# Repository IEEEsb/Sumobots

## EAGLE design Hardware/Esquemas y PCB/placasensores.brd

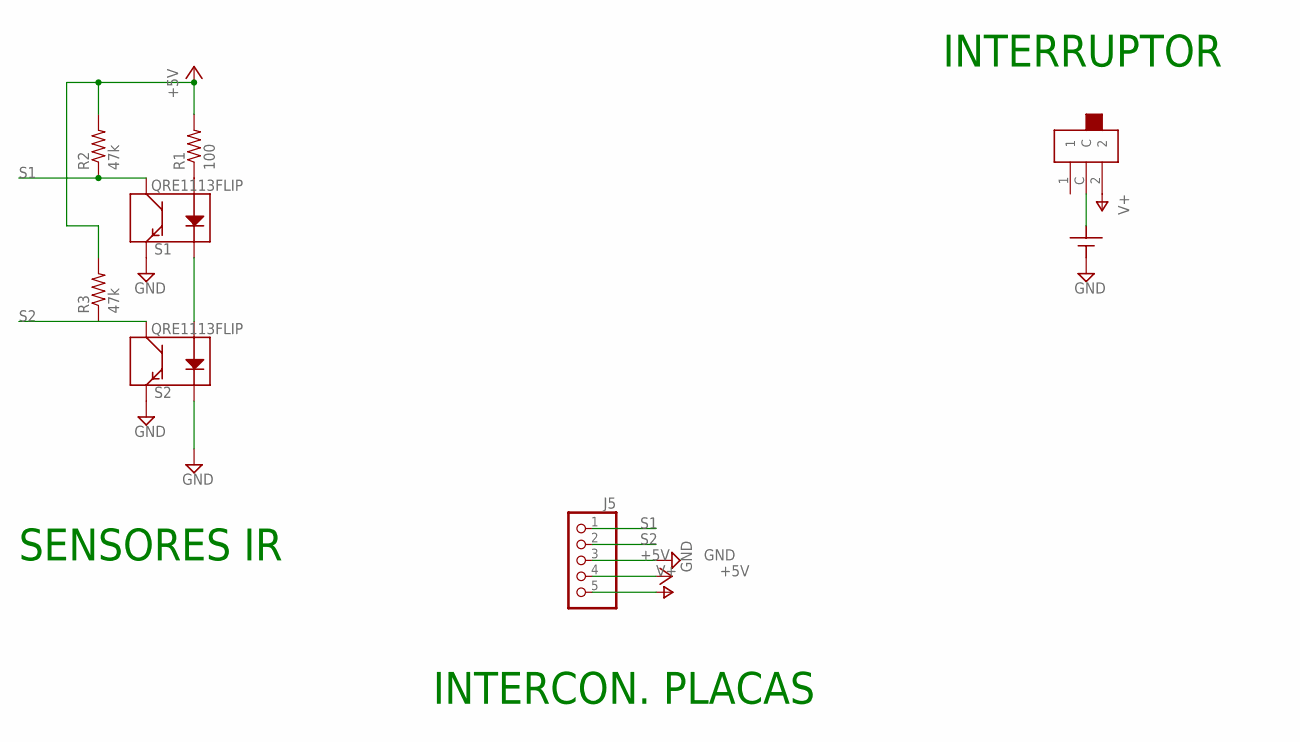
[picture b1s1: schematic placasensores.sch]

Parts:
J5: PINHD-1X5; 1X05
R1: 100; 1206
R2, R3: 47k; 1206
S1, S2: QRE1113FLIP; QRE1113GR_HOLE
SW1: SK-12D07G3
U$3: 5XAA; 5XAAHOLDER

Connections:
+5V: J5.4, R1.2, R2.2, R3.2
GND: J5.3, S1.E, S2.E, S2.K, U$3.P$2
unnamed: S1.K, S2.A
unnamed: R1.1, S1.A
unnamed: SW1.C, U$3.P$1
S1: J5.1, R2.1, S1.C
S2: J5.2, R3.1, S2.C
V+: J5.5, SW1.2

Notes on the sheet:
SENSORES IR
INTERCON. PLACAS
INTERRUPTOR

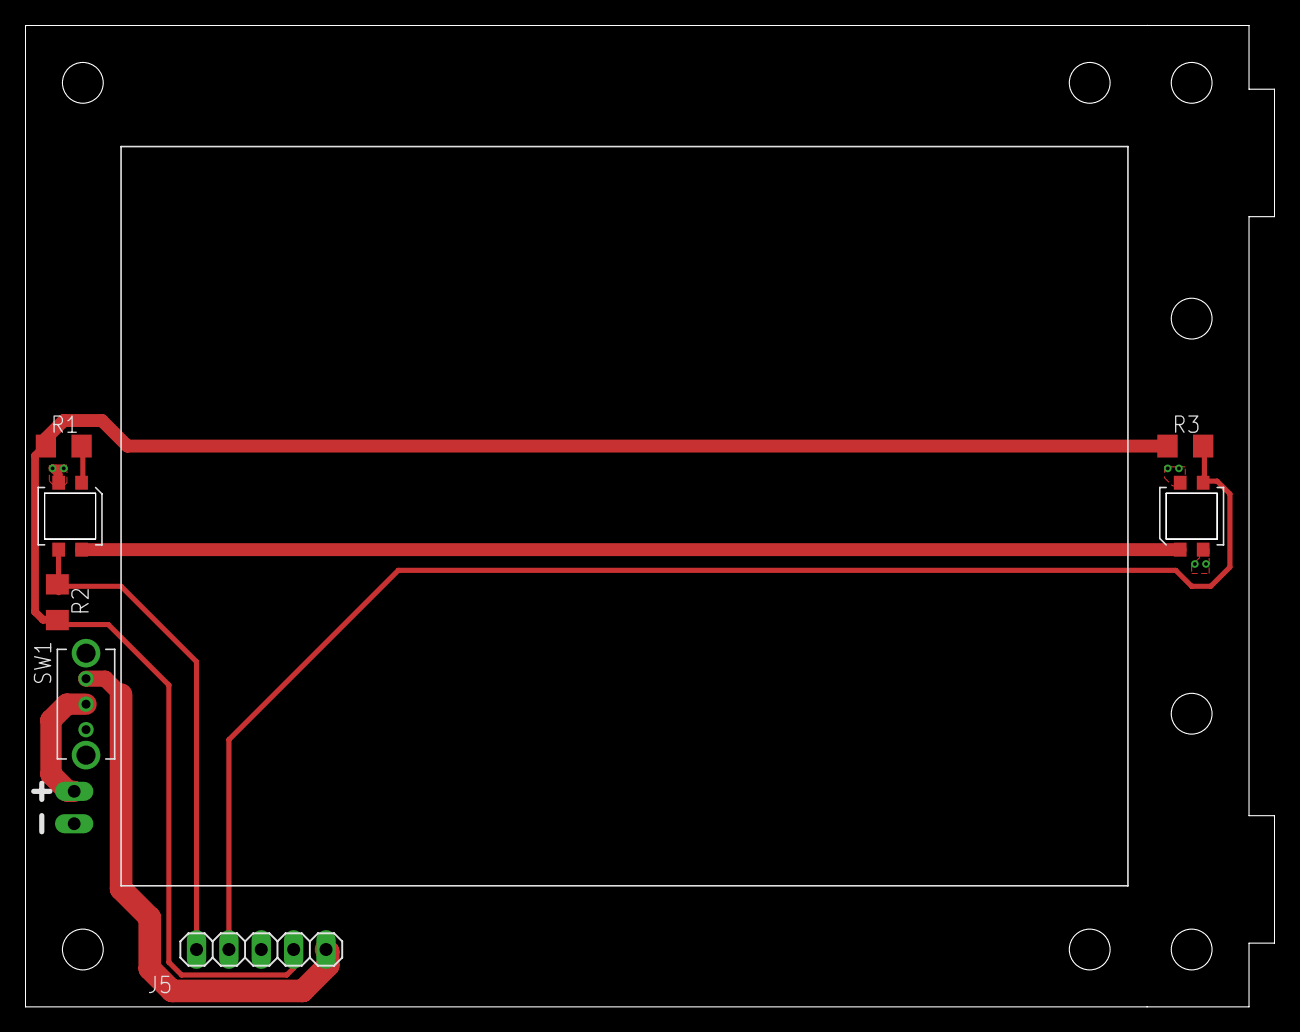
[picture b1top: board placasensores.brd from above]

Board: 2 copper layers, 98.0 x 77.0 mm, 8 parts (0 on the bottom side), 8 nets.

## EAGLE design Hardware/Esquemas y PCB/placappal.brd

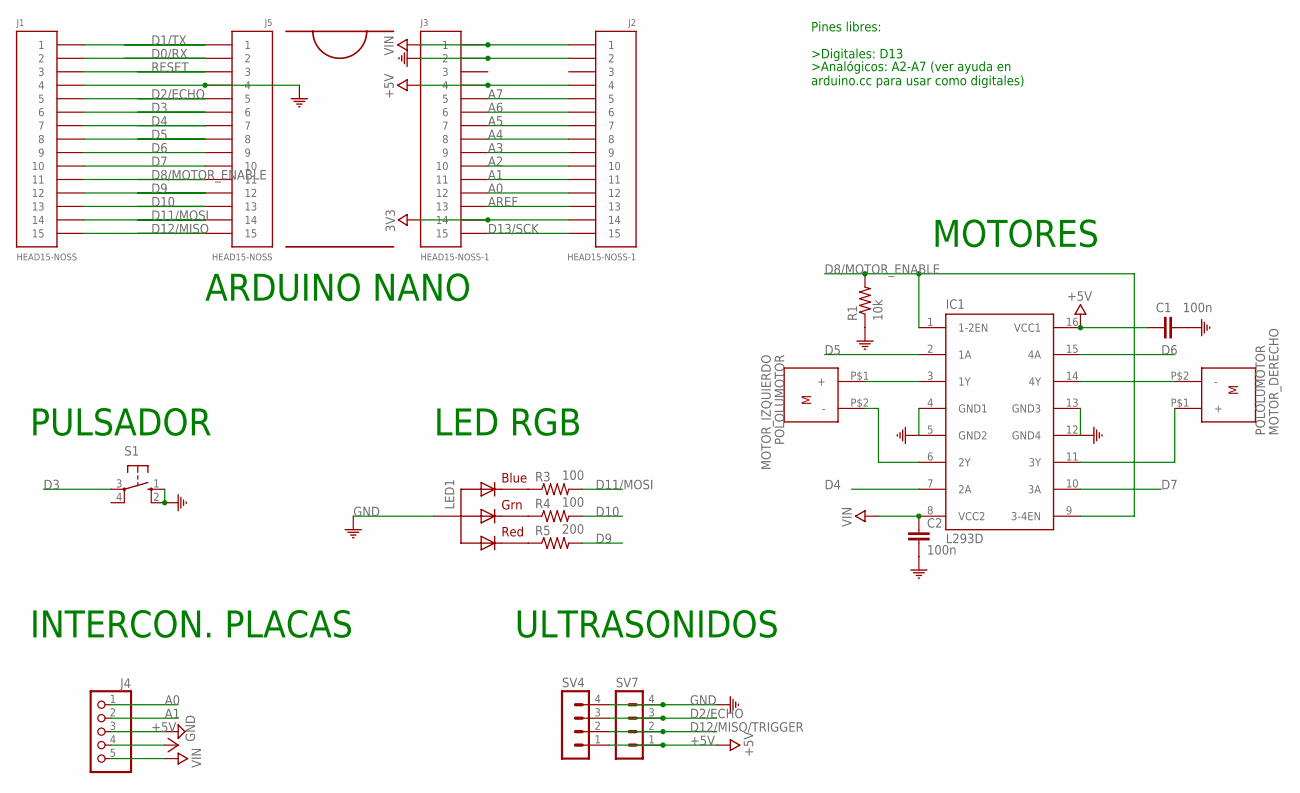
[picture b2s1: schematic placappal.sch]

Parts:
C1, C2: 100n; 1206
IC1: L293D; DIL16
J1, J5: HEAD15-NOSS
J2, J3: HEAD15-NOSS-1
J4: PINHD-1X5; 1X05
LED1: RGBLED_CA-5MM; LED5MMRGB
MOTOR_DERECHO: POLOLUMOTOR; N20MOTOR
MOTOR_IZQUIERDO: POLOLUMOTOR; N20MOTOR
R1: 10k; 1206
R3, R4: 100; 1206
R5: 200; 1206
S1: 10-XX; B3F-10XX
SV4, SV7: MA04-1

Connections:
3V3: J2.14, J3.14
+5V: C1.2, IC1.16 (VCC1), J2.4, J3.4, J4.4, SV4.1, SV7.1
A0: J2.12, J3.12, J4.1
A1: J2.11, J3.11, J4.2
A2: J2.10, J3.10
A3: J2.9, J3.9
A4: J2.8, J3.8
A5: J2.7, J3.7
A6: J2.6, J3.6
A7: J2.5, J3.5
AREF: J2.13, J3.13
D0/RX: J1.2, J5.2
D1/TX: J1.1, J5.1
D2/ECHO: J1.5, J5.5, SV4.3, SV7.3
D3: J1.6, J5.6, S1.3
D4: IC1.7 (2A), J1.7, J5.7
D5: IC1.2 (1A), J1.8, J5.8
D6: IC1.15 (4A), J1.9, J5.9
D7: IC1.10 (3A), J1.10, J5.10
D8/MOTOR_ENABLE: IC1.1 (1-2EN), IC1.9 (3-4EN), J1.11, J5.11, R1.2
D9: J1.12, J5.12, R5.2
D10: J1.13, J5.13, R4.2
D11/MOSI: J1.14, J5.14, R3.2
D12/MISO: J1.15, J5.15
D12/MISO/TRIGGER: SV4.2, SV7.2
D13/SCK: J2.15, J3.15
GND: C1.1, C2.2, IC1.4 (GND1), IC1.5 (GND2), IC1.12 (GND4), IC1.13 (GND3), J1.4, J2.2, J3.2, J4.3, J5.4, LED1.2 (VCC), R1.1, S1.1 (S), S1.2 (S1), SV4.4, SV7.4
unnamed: IC1.3 (1Y), MOTOR_IZQUIERDO.P$1 (+)
unnamed: IC1.6 (2Y), MOTOR_IZQUIERDO.P$2 (-)
unnamed: IC1.14 (4Y), MOTOR_DERECHO.P$2 (-)
unnamed: IC1.11 (3Y), MOTOR_DERECHO.P$1 (+)
unnamed: LED1.4 (BLUE), R3.1
unnamed: LED1.3 (GREEN), R4.1
unnamed: LED1.1 (RED), R5.1
RESET: J1.3, J5.3
VIN: C2.1, IC1.8 (VCC2), J2.1, J3.1, J4.5

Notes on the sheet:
ARDUINO NANO
PULSADOR
LED RGB
INTERCON. PLACAS
ULTRASONIDOS
MOTORES
Pines libres:

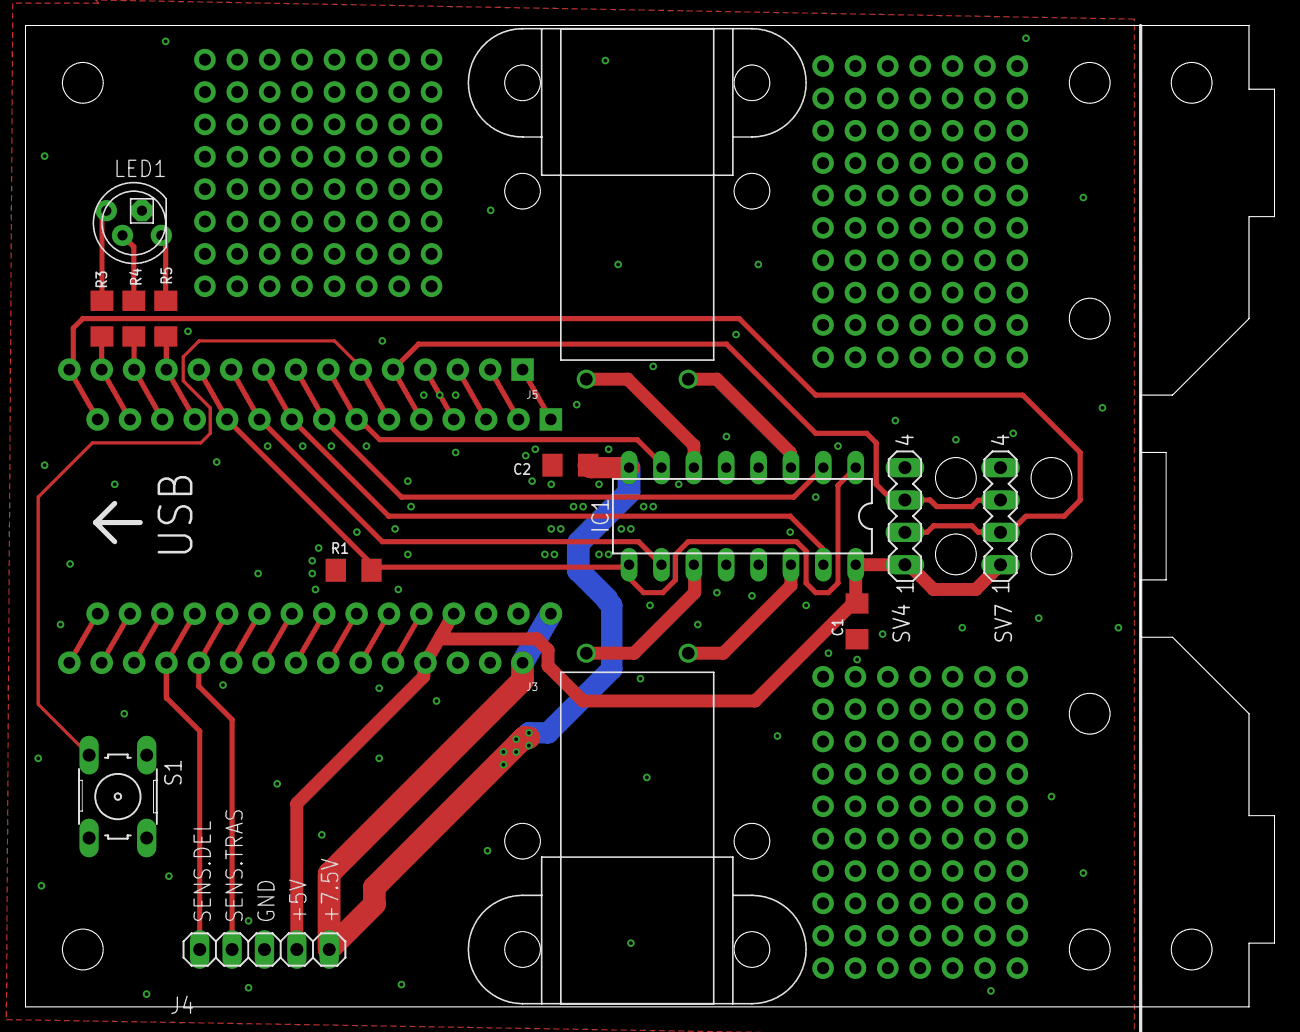
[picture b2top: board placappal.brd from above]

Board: 2 copper layers, 98.0 x 77.0 mm, 18 parts (0 on the bottom side), 36 nets.

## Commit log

2014-05-29 Initial commit
    Sumobots code
2014-07-18 Better algorithm
2014-07-18 Added documentation
2014-07-18 Cleanup

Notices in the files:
parts and their libraries:
SparkFun-Passives: Licensing: CC v3.0 Share-Alike You are welcome to use this library for commercial purposes.
